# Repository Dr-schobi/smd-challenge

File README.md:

# SMD soldering challenge

https://user-images.githubusercontent.com/78444256/188329124-fbfda367-b1dc-41d7-a8d5-ee6e349dee65.mp4

This project is about hand-soldering tiny SMD components onto a PCB. Similar to [Defcon](https://dchhv.org/events/smdsolderchallenge.html) in [2018](https://hackaday.com/2018/08/02/smd-soldering-challenge-lands-at-def-con/).

My goals:
- I wanna try! (both with and without extra tools).
  In the past, I've done some PCB development, debugging, soldering and measuring around 2008 for developing digital cameras, with large FPGAs (Xilinx Vertex), my own DDR memory controller on complex 10+ layer PCBs. Back then, this was no 0201 and I'm much older now with many years of just Matlab coding and only little electronics. 

- I don't think that I will succeed on the first try.
  I will need more than one shot with the tiny components, especially towards 0201. 
  the kit from the set above comes with one component each - this might not be enough.

- Learn some more! 
  The new Kicad 6 looks realy good and I'm lacking practice in PCB design, this looks like a good chance for a quick project with focus on aesthetics.   
  I've not worked wit Atmel microcontrollers for over 15 years - time to refresh.
  
- Maybe this is for sharing?
  In the last years, I met a few electronics developers who might like to be gifted a kit. I'm certainly not going to order just one set.

Status:
- PCBs have arrived, assembled and code is working

Errata: 
- silkscreen says "0806", should be "0805"

# Schematic and PCB

changes I made (on purpose)
- two LEDs per type, flip one other than the first, and everything will light up
- all LEDs in the center, I'm looking for an icicle christmas decoration effect of dropping light
- all LEDs wired to the controller, should be ably to drive one at a time, in any orientation

# Components

I put together a list of components I ordered from LCSC:

Resistors  (package, value, number of pieces I ordered, description):
- 0201 R 330Ohm    500  UNI-ROYAL(Uniroyal Elec) 0201WMF3300TEE   [LCSC Part # C516485](https://lcsc.com/product-detail/Chip-Resistor-Surface-Mount_UNI-ROYAL-Uniroyal-Elec-0201WMF3300TEE_C516485.html)
- 0201 R 330Ohm    500  Walsin Tech Corp WR02X3300FTL       [LCSC Part # C367585](https://lcsc.com/product-detail/Chip-Resistor-Surface-Mount_Walsin-Tech-Corp-WR02X3300FTL_C367585.html)
- 0402 R 330Ohm    300  FOJAN FRC0402F3300TS                [LCSC Part # C2930002](https://lcsc.com/product-detail/Chip-Resistor-Surface-Mount_FOJAN-FRC0402F3300TS_C2930002.html)
- 0603 R 330Ohm    300  FOJAN FRC0603F3300TS                [LCSC Part # C2933198](https://lcsc.com/product-detail/Chip-Resistor-Surface-Mount_FOJAN-FRC0603F3300TS_C2933198.html)
- 0803 R 330Ohm    300  FOJAN FRC0805F3300TS                [LCSC Part # C2930157](https://lcsc.com/product-detail/Chip-Resistor-Surface-Mount_FOJAN-FRC0805F3300TS_C2930157.html)
- 1206 R 330Ohm    300  FOJAN FRC1206F3300TS                [LCSC Part # C2933675](https://lcsc.com/product-detail/Chip-Resistor-Surface-Mount_FOJAN-FRC1206F3300TS_C2933675.html)
- 1210 R 330Ohm    150  FOJAN FRC1210F3300TS                [LCSC Part # C2933817](https://lcsc.com/product-detail/Chip-Resistor-Surface-Mount_FOJAN-FRC1210F3300TS_C2933817.html)

LEDs (package, value, number of pieces I ordered, description):
- 0201 LED red   150   XINGLIGHT XL-0201SURC        [LCSC Part # C3646923](https://lcsc.com/product-detail/Light-Emitting-Diodes-LED_XINGLIGHT-XL-0201SURC_C3646923.html)
- 0402 LED red   100   XINGLIGHT XL-1005SURC        [LCSC Part # C965790](https://lcsc.com/product-detail/Light-Emitting-Diodes-LED_XINGLIGHT-XL-1005SURC_C965790.html)
- 0603 LED red   100   XINGLIGHT XL-1608SURC-06     [LCSC Part # C965799](https://lcsc.com/product-detail/Light-Emitting-Diodes-LED_XINGLIGHT-XL-1608SURC-06_C965799.html)
- 0805 LED red   100   XINGLIGHT XL-2012SURC        [LCSC Part # C965812](https://lcsc.com/product-detail/Light-Emitting-Diodes-LED_XINGLIGHT-XL-2012SURC_C965812.html)
- 1206 LED red   100   TUOZHAN P2-1206RTCS2-0.9T-F  [LCSC Part # C2827254](https://lcsc.com/product-detail/Light-Emitting-Diodes-LED_TUOZHAN-P2-1206RTCS2-0-9T-F_C2827254.html)
- 1210 LED red   100   XINGLIGHT XL-3227SURUGC      [LCSC Part # C965842](https://lcsc.com/product-detail/Light-Emitting-Diodes-LED_XINGLIGHT-XL-3227SURUGC_C965842.html)

Others
- 0603 C 10uF10V  100    Samsung Electro-Mechanics CL10A106KP8NNNC  [LCSC Part # C19702](https://lcsc.com/product-detail/Multilayer-Ceramic-Capacitors-MLCC-SMD-SMT_Samsung-Electro-Mechanics-CL10A106KP8NNNC_C19702.html)
- SIOC-8 150mil  15x    Microchip Tech ATTINY13A-SSU   [LCSC Part # C14075](https://lcsc.com/product-detail/ATMEL-AVR_Microchip-Tech-ATTINY13A-SSU_C14075.html)
- Batt    15x   Q&J CR2032-BS-6-1   [LCSC Part # C70377](https://lcsc.com/product-detail/Battery-Connectors_Q-J-CR2032-BS-6-1_C70377.html)

# Results

I packed a few kits with a programmed Attiny13 already on the board. I'm waiting for assembly feedback.

# Power consumption
measured with 3V supply and 12Ohm resistor
- 12x LED flash of 5msec, 42mV -> 3.5mA, energy of 17.5 mA msec
- 12x pause between flashes 375msec, <0.01mA, energy of 3.75 mA msec
- long pause 1.5sec, <0.01mA, energy of 15 mA msec

Total of 6060msec and energy of 270 mA msec, average current of 0.045mA
In theory, a CR2032 coin cell with 120mAh could last >100 days - let's see.

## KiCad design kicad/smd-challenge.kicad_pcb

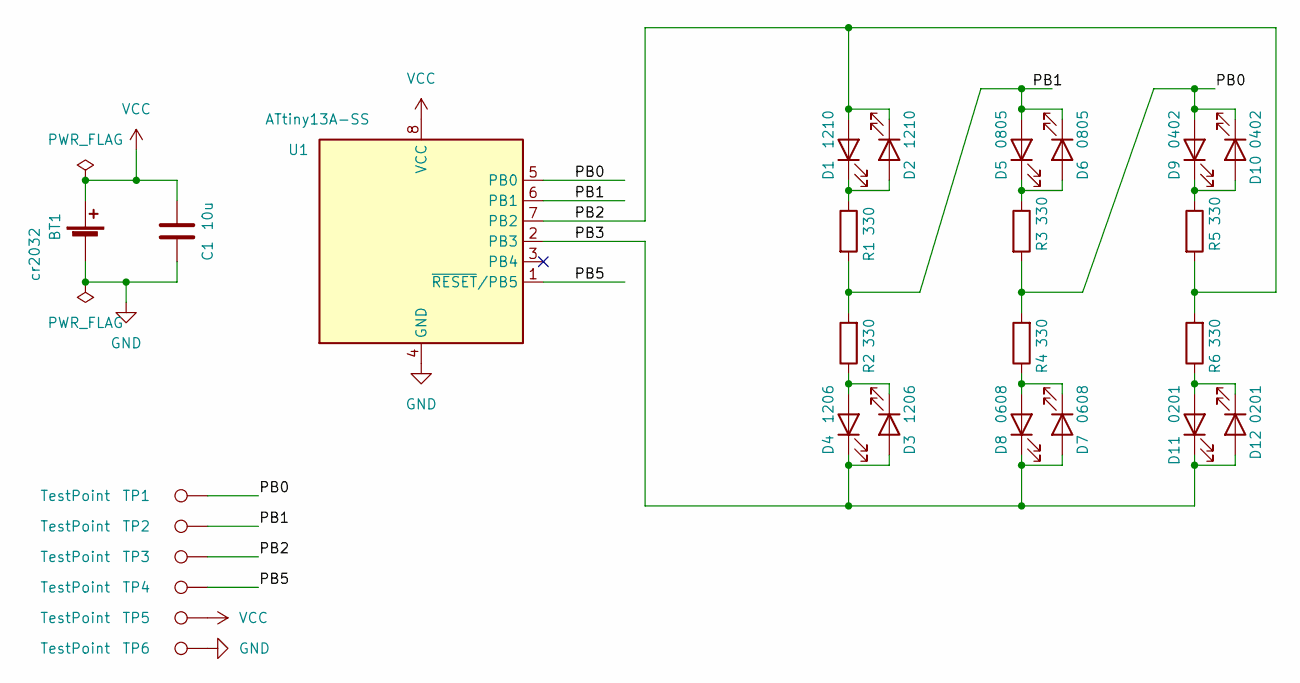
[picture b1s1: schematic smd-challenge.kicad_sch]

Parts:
BT1: cr2032; BatteryHolder_Keystone_1060_1x2032
C1: 10u; C_0805_2012Metric_Pad1.18x1.45mm_HandSolder
D1, D2: 1210; LED_1210_3225Metric_Pad1.42x2.65mm_HandSolder
D3, D4: 1206; LED_1206_3216Metric_Pad1.42x1.75mm_HandSolder
D5, D6: 0805; LED_0805_2012Metric_Pad1.15x1.40mm_HandSolder
D7, D8: 0608; LED_0603_1608Metric_Pad1.05x0.95mm_HandSolder
D9, D10: 0402; LED_0402_1005Metric_Pad0.77x0.64mm_HandSolder
D11, D12: 0201; LED_0201_0603Metric_Pad0.64x0.40mm_HandSolder
R1: 330; R_1210_3225Metric_Pad1.30x2.65mm_HandSolder
R2: 330; R_1206_3216Metric_Pad1.30x1.75mm_HandSolder
R3: 330; R_0805_2012Metric_Pad1.20x1.40mm_HandSolder
R4: 330; R_0603_1608Metric_Pad0.98x0.95mm_HandSolder
R5: 330; R_0402_1005Metric_Pad0.72x0.64mm_HandSolder
R6: 330; R_0201_0603Metric_Pad0.64x0.40mm_HandSolder
TP1, TP2, TP3, TP4, TP5, TP6: TestPoint; TestPoint_Pad_D1.5mm
U1: ATtiny13A-SS; SOIC-8_3.9x4.9mm_P1.27mm; LCSC C14075

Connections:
/PB0: D9.2 (A), D10.1 (K), R3.2, R4.2, TP1.1, U1.5 (PB0)
/PB1: D5.2 (A), D6.1 (K), R1.2, R2.2, TP2.1, U1.6 (PB1)
/PB2: D1.2 (A), D2.1 (K), R5.2, R6.2, TP3.1, U1.7 (PB2)
/PB3: D3.2 (A), D4.1 (K), D7.2 (A), D8.1 (K), D11.1 (K), D12.2 (A), U1.2 (PB3)
/PB5: TP4.1, U1.1 (~RESET/PB5)
GND: BT1.2 (-), C1.2, TP6.1, U1.4 (GND)
unnamed: D1.1 (K), D2.2 (A), R1.1
unnamed: D3.1 (K), D4.2 (A), R2.1
unnamed: D5.1 (K), D6.2 (A), R3.1
unnamed: D7.1 (K), D8.2 (A), R4.1
unnamed: D9.1 (K), D10.2 (A), R5.1
unnamed: D11.2 (A), D12.1 (K), R6.1
VCC: BT1.1 (+), C1.1, TP5.1, U1.8 (VCC)

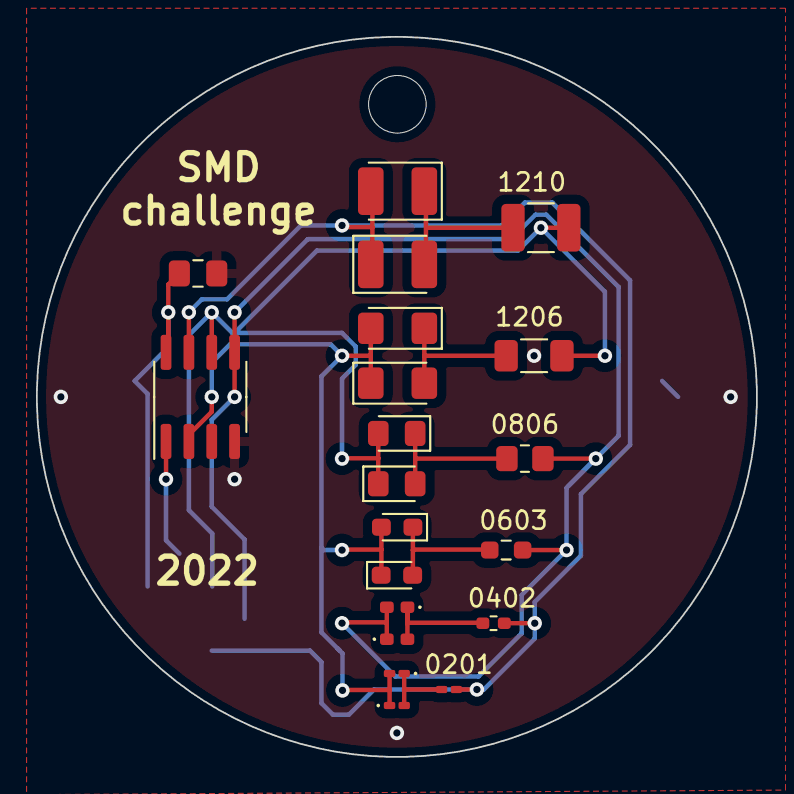
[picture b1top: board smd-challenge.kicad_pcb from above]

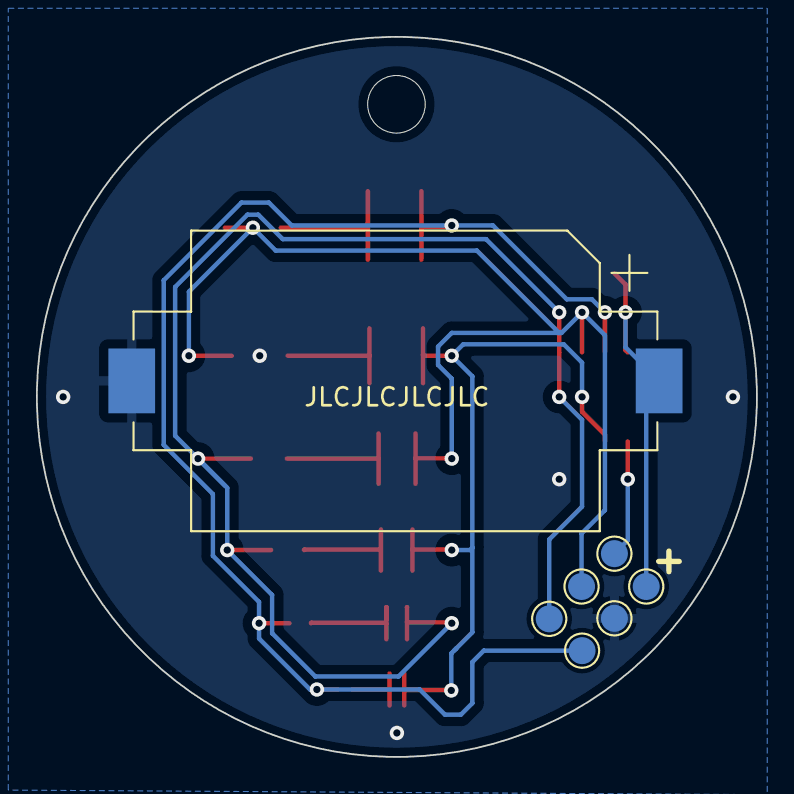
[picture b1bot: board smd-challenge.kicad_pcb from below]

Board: 2 copper layers, 40.0 x 40.0 mm, 27 parts (7 on the bottom side), 13 nets.

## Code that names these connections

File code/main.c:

#include <avr/io.h>
#include <util/delay.h>
#include <avr/sleep.h>
#include <avr/wdt.h>
#include <avr/interrupt.h>

void blink(int A, int B) {

    // enable LED from A to B
    DDRB = ( 1 << A ) | ( 1 << B );
    PORTB |= ( 1 << A ); 
    PORTB &= ~( 1 << B );
    _delay_ms(5);
    DDRB = 0;
    
    WDTCR = _BV(WDTIE) |  _BV(WDP1) | _BV(WDP0);    // enable WDT Interrupt, Set WDT 125MS
    wdt_reset();
    sei();
    sleep_mode();
    cli();
    
    WDTCR = _BV(WDTIE) |  _BV(WDP2);    // enable WDT Interrupt, Set WDT 250MS
    wdt_reset();
    sei();
    sleep_mode();
    cli();

}

ISR(WDT_vect) { 

}



int main( void ) {
    
    set_sleep_mode(SLEEP_MODE_PWR_DOWN);
 
    while( 1 ) {       
             
        blink( PB2, PB1 );
        blink( PB1, PB2 );

        blink( PB3, PB1 );
        blink( PB1, PB3 );
        
        blink( PB1, PB0 );
        blink( PB0, PB1 );

        blink( PB3, PB0 );
        blink( PB0, PB3 );
        
        blink( PB0, PB2 );
        blink( PB2, PB0 );
        
        blink( PB3, PB2 );
        blink( PB2, PB3 );


        WDTCR = _BV(WDTIE) |  _BV(WDP2) | _BV(WDP1);    // enable WDT Interrupt, Set WDT 1S    
        wdt_reset();
        sei();
        sleep_mode();
        cli();

        WDTCR = _BV(WDTIE) |  _BV(WDP2) | _BV(WDP0);    // enable WDT Interrupt, Set WDT 500MS
        wdt_reset();
        sei();
        sleep_mode();
        cli();
  
    }
 
    return 0;
}

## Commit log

2022-07-28 added files and descriptions
2022-07-28 added some more grafics, screenshots
2022-09-03 added code for LED blinking and smd assembly instructions
2022-09-04 updated documentation and results photos
